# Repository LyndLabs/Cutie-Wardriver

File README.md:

# Cutie Wardriver ❤️📡
### **The cute ESP32-based pocket wardriver!**

## Features:
- Xiao / QT-Py compatible
- SH1106 OLED
- MicroSD Card
- LiPo Battery (charging + meter)
- Qwiic Connector

## Firmware:
More docs coming soon.  Check out the [official firmware repo](https://github.com/LyndLabs/Cutie-Wardriver-Firmware)!

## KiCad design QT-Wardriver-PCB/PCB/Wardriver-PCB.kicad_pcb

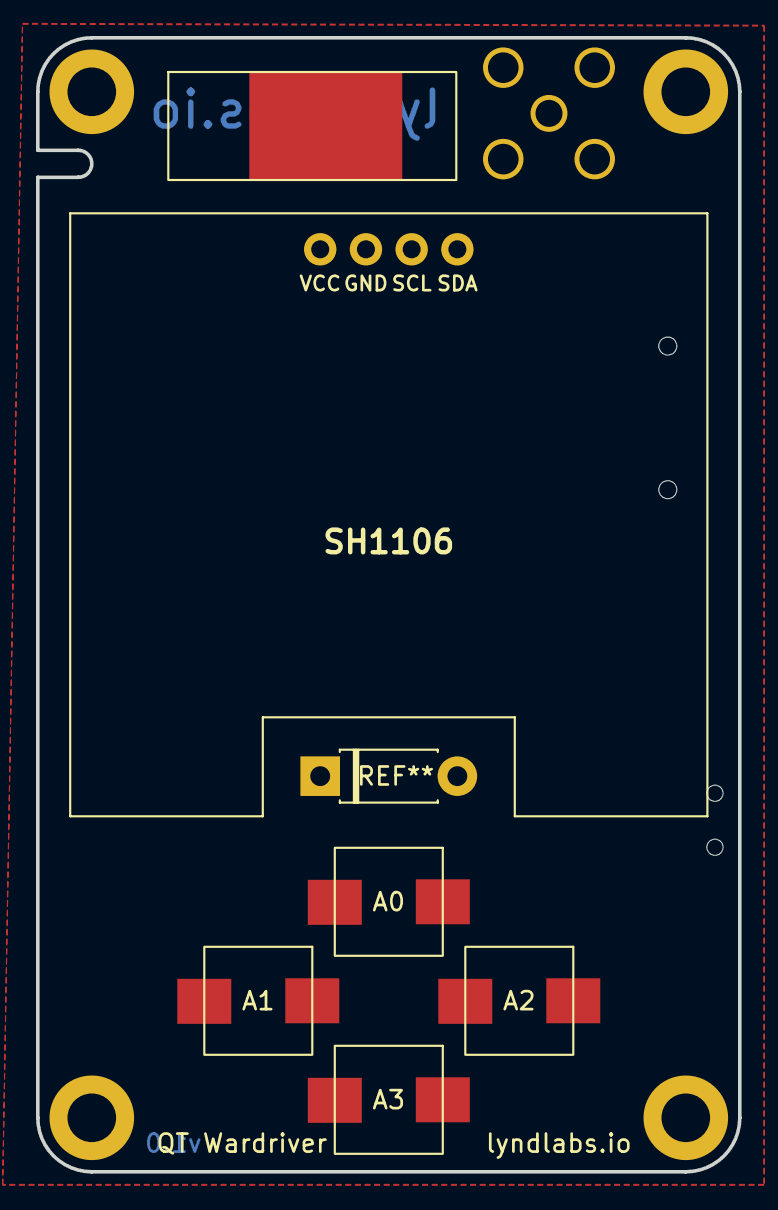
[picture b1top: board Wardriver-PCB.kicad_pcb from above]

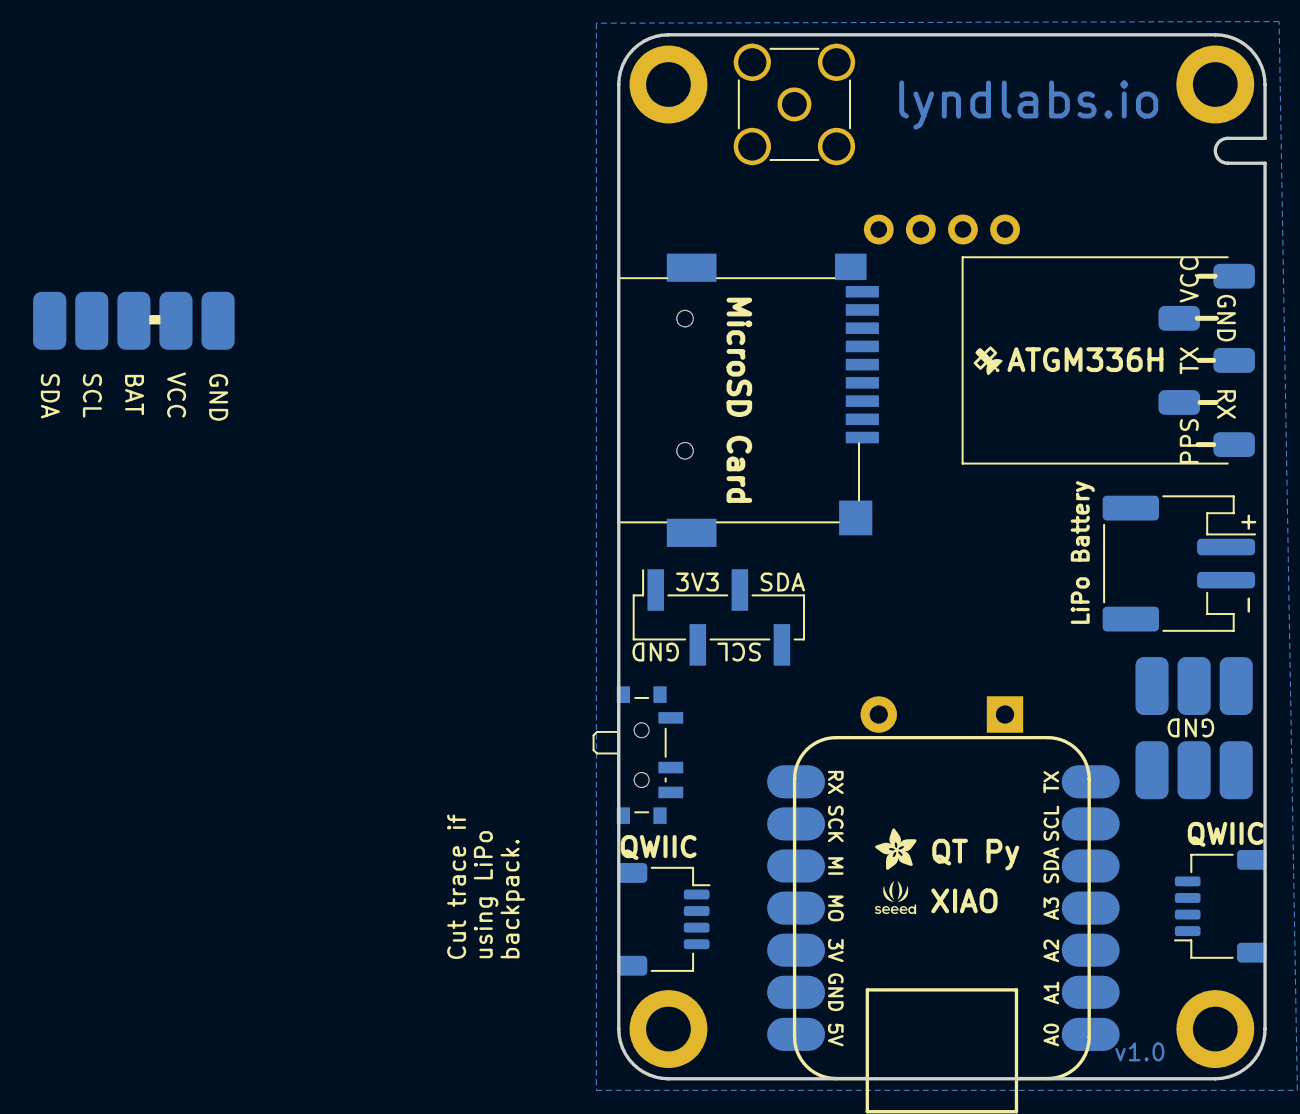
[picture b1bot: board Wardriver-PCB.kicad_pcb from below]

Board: 2 copper layers, 39.0 x 63.0 mm, 12 parts (7 on the bottom side), 13 nets, no tracks yet.

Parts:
J1: MICRO-SD CARD; MicroSD
J2: Conn_01x02_Female; JST_PH_S2B-PH-SM4-TB_1x02-1MP_P2.00mm_Horizontal
J3: Qwiic Connector; JST_SH_SM04B-SRSS-TB_1x04-1MP_P1.00mm_Horizontal
J3#2: QWIIC; JST_SH_SM04B-SRSS-TB_1x04-1MP_P1.00mm_Horizontal
J5: Expansion Header; PinHeader_1x04_P2.54mm_Vertical_SMD_Pin1Right
SW1: Up; Smol
SW2: Left; Smol
SW3: Right; Smol
SW4: Down; Smol
U1: XIAO ESP32-S2; MOUDLE14P-SMD-2.54-21X17.8MM
U2: ATGM336H; ATGM336H-GPS
U3: ATGM336H; SH1106

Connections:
+3V3: J1.4 (VDD), J3.2, J3#2.2, J5.2, U1.12 (3V3), U2.1 (VCC), U3.1 (VCC)
DN-Btn: SW4.1, U1.4 (PA11_A3_D3)
GND: J1.2 (DAT3/CD), J1.6 (VSS), J1.11 (SHIELD), J3.1, J3#2.1, J5.1, SW1.2 (1), SW2.2 (1), SW3.2 (1), SW4.2 (1), U1.13 (GND), U2.2 (VCC), U3.2 (GND)
LT-Btn: SW2.1, U1.2 (PA4_A1_D1)
MISO: J1.7 (DAT0), U1.10 (PA5_A9_D9_MISO)
MOSI: J1.3 (CMD), U1.11 (PA6_A10_D10_MOSI)
RT-Btn: SW3.1, U1.3 (PA10_A2_D2)
RX: U1.8 (PB09_D7_RX), U2.3 (VCC)
SCK: J1.5 (CLK), U1.9 (PA7_A8_D8_SCK)
SCL: J3.4, J3#2.4, J5.4, U1.6 (PA9_A5_D5_SCL), U3.3 (TX)
SDA: J3.3, J3#2.3, J5.3, U1.5 (PA8_A4_D4_SDA), U3.4 (RX)
TX: U1.7 (PB08_A6_TX), U2.4 (VCC)
UP-Btn: SW1.1, U1.1 (PA02_A0_D0)

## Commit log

2023-10-30 add v1.0 QT Wardriver source & gerbers
2023-11-01 change via size for optimized manufacturing
2023-12-16 changing board layout
2023-12-16 add mockup 3d file
2023-12-16 downgrade to version 0.0
2024-01-14 publish v0.1 Cutie Wardriver design files
2024-01-14 rename QT Wardriver --> Cutie Wardriver
2024-01-14 rename QT -> Cutie
2024-01-19 push v0.2 files & image
2024-01-27 add backplate designs
2024-01-27 upload enclosure rev1 1 files
2024-01-27 add D-Pad files
2024-01-28 push backplate + DPAD
